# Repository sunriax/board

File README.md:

# BOARD Repository!

## Description

The BOARD repository is a set of Schematic and PCB files which can be used to build adapters for the STK500/STK600, Basys3 and other platforms. The design was made with Eagle and can be adapted easily. The Gerber files can also be found in the repository. We recommend to let [Elecrow](https://www.elecrow.com/) produce the PCB.

## Layouts

* [LCD Display Adapter](./display/display.md)
* [LCD Display Controller](./controller/controller.md)

## Important Notice

This files are valid for all repositories at the SUNriaX Github!
* [Readme](https://github.com/sunriax/manual/blob/master/README.md)
* [License](https://github.com/sunriax/manual/blob/master/LICENSE.md)
* [Warranty](https://github.com/sunriax/manual/blob/master/WARRANTY.md)

## Additional Information

You can find more additional information in the [manual](https://github.com/sunriax/manual/tree/master/docs) repository and/or visit the [WIKI](https://wiki.sunriax.at/) for further information (currently under construction).

If there are any further questions feel free to start an issue or contact us, we try to react as quick as possible.

---
**R. GÄCHTER, Rankweil Oct/2019**

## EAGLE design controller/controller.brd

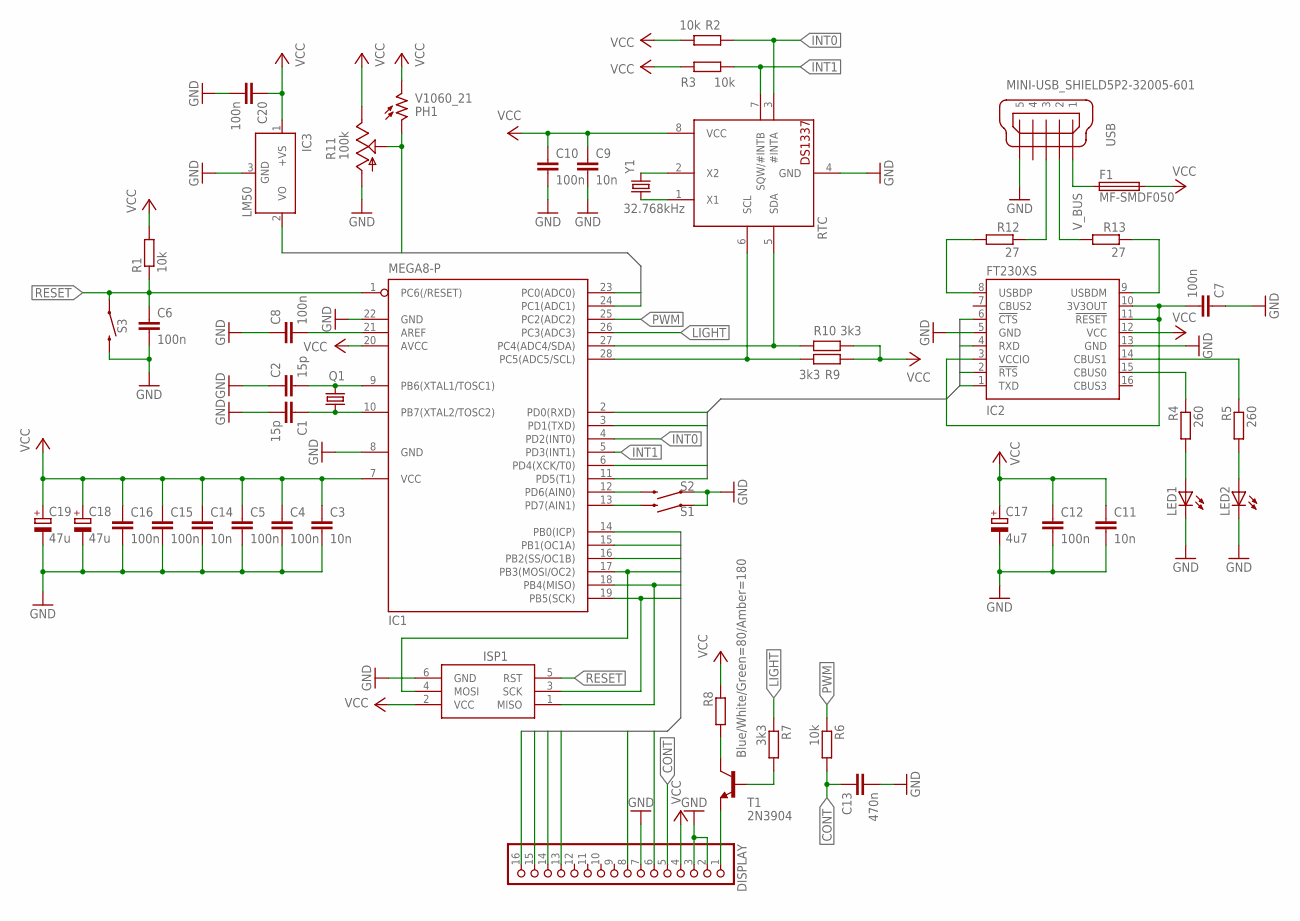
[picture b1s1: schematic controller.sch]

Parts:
C1, C2: 15p; C025-024X044
C3, C9, C11, C14: 10n; C025-024X044
C4, C5, C6, C7, C8, C10, C12, C15, C16, C20: 100n; C025-024X044
C13: 470n; C025-024X044
C17: 4u7; E1,8-4
C18, C19: 47u; E1,8-4
DISPLAY: PINHD-1X16; 1X16
F1: MF-SMDF050
IC1: MEGA8-P; DIL28-3
IC2: FT230XS; SSOP16
IC3: LM50; SOT23
ISP1: AVRISP-6; AVRISP
LED1, LED2: LED_ELD260; LED_LD260
PH1: V1060_21; TO-5_V10
Q1: CRYSTALHC18U-V; HC18U-V
R1, R2, R3, R6: 10k; 0207/10
R4, R5: 260; 0207/10
R7, R9, R10: 3k3; 0207/10
R8: Blue/White/Green=80/Amber=180; 0207/10
R11: 100k; CT6
R12, R13: 27; R0603
RTC: DS1337; DIL08-ROUND
S1, S2, S3: MOMENTARY-SWITCH-SPST-PTH-6.0MM; TACTILE_SWITCH_PTH_6.0MM
T1: 2N3904; TO92
USB: MINI-USB_SHIELD5P2-32005-601; 32005-601
Y1: 32.768kHz; CRYSTAL-PTH-2X6-CYL

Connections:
ADC0: IC1.23 (PC0(ADC0)), IC3.2 (VO)
ADC1: IC1.24 (PC1(ADC1)), PH1.1, R11.S
CONT: C13.1, DISPLAY.5, R6.2
CTS: IC1.6 (PD4(XCK/T0)), IC2.6 (!CTS)
DB4: DISPLAY.13, IC1.17 (PB3(MOSI/OC2)), ISP1.4 (MOSI)
DB5: DISPLAY.14, IC1.16 (PB2(SS/OC1B))
DB6: DISPLAY.15, IC1.15 (PB1(OC1A))
DB7: DISPLAY.16, IC1.14 (PB0(ICP))
E: DISPLAY.8, IC1.18 (PB4(MISO)), ISP1.1 (MISO)
GND: C1.2, C2.1, C3.2, C4.2, C5.2, C6.2, C7.1, C8.1, C9.2, C10.2, C11.2, C12.2, C13.2, C14.2, C15.2, C16.2, C17.-, C18.-, C19.-, C20.2, DISPLAY.2, DISPLAY.3, DISPLAY.7, IC1.8 (GND), IC1.22 (GND), IC2.5 (GND), IC2.13 (GND), IC3.3 (GND), ISP1.6 (GND), LED1.K (C), LED2.K (C), R11.A, RTC.4 (GND), S1.1, S2.1, S3.3 (2), USB.5
INT0: IC1.4 (PD2(INT0)), R2.1, RTC.3 (#INTA)
INT1: IC1.5 (PD3(INT1)), R3.2, RTC.7 (SQW/#INTB)
LIGHT: IC1.26 (PC3(ADC3)), R7.1
unnamed: C2.2, IC1.9 (PB6(XTAL1/TOSC1)), Q1.2
unnamed: C1.1, IC1.10 (PB7(XTAL2/TOSC2)), Q1.1
unnamed: R13.2, USB.2
unnamed: C8.2, IC1.21 (AREF)
unnamed: IC2.15 (CBUS0), R4.1
unnamed: R12.1, USB.3
unnamed: IC1.12 (PD6(AIN0)), S2.3 (2)
unnamed: IC1.13 (PD7(AIN1)), S1.3 (2)
unnamed: IC2.8 (USBDP), R12.2
unnamed: IC2.9 (USBDM), R13.1
unnamed: C7.2, IC2.3 (VCCIO), IC2.10 (3V3OUT), IC2.11 (!RESET)
unnamed: IC2.14 (CBUS1), R5.1
unnamed: LED1.A, R4.2
unnamed: LED2.A, R5.2
unnamed: DISPLAY.1, T1.3 (E)
unnamed: RTC.2 (X2), Y1.1
unnamed: R7.2, T1.2 (B)
unnamed: R8.2, T1.1 (C)
unnamed: IC1.28 (PC5(ADC5/SCL)), R9.2, RTC.6 (SCL)
unnamed: IC1.27 (PC4(ADC4/SDA)), R10.1, RTC.5 (SDA)
unnamed: RTC.1 (X1), Y1.2
PWM: IC1.25 (PC2(ADC2)), R6.1
RESET: C6.1, IC1.1 (PC6(/RESET)), ISP1.5 (RST), R1.1, S3.1
RS: DISPLAY.6, IC1.19 (PB5(SCK)), ISP1.3 (SCK)
RTS: IC1.11 (PD5(T1)), IC2.2 (!RTS)
RXD: IC1.3 (PD1(TXD)), IC2.4 (RXD)
TXD: IC1.2 (PD0(RXD)), IC2.1 (TXD)
VCC: C3.1, C4.1, C5.1, C9.1, C10.1, C11.1, C12.1, C14.1, C15.1, C16.1, C17.+, C18.+, C19.+, C20.1, DISPLAY.4, F1.2, IC1.7 (VCC), IC1.20 (AVCC), IC2.12 (VCC), IC3.1 (+VS), ISP1.2 (VCC), PH1.2, R1.2, R2.2, R3.1, R8.1, R9.1, R10.2, R11.E, RTC.8 (VCC)
V_BUS: F1.1, USB.1

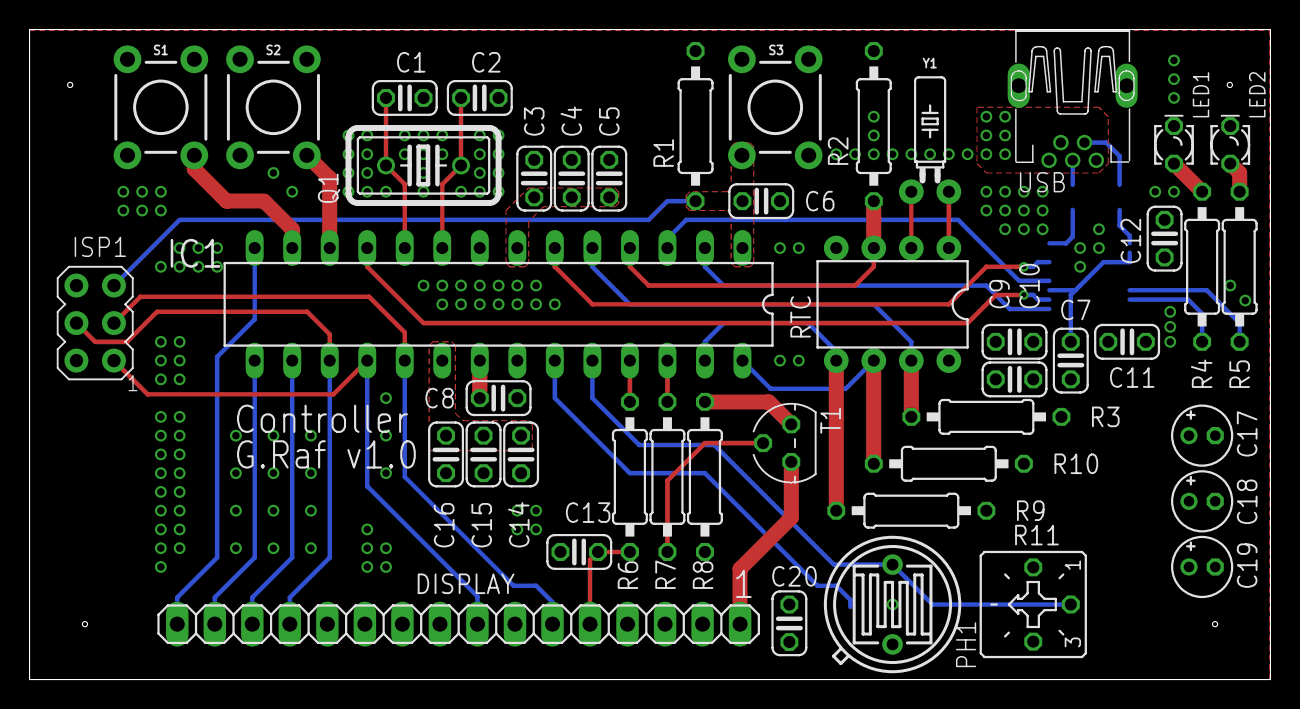
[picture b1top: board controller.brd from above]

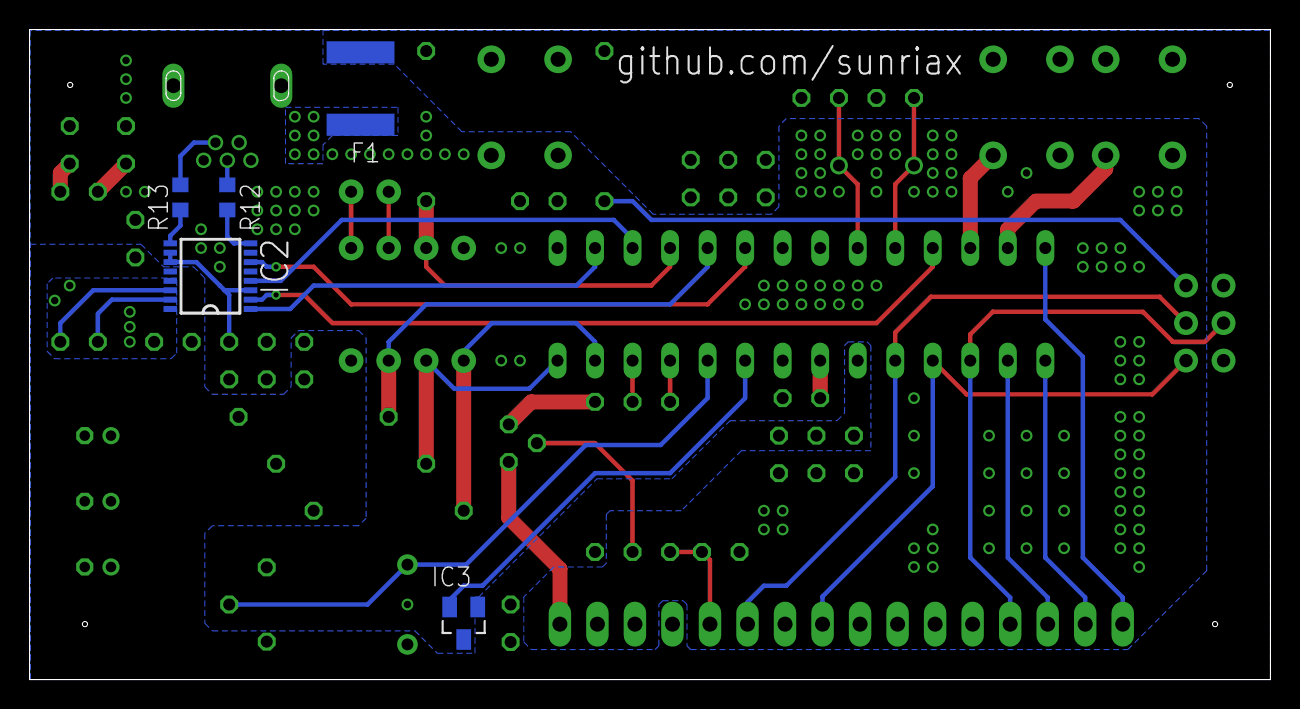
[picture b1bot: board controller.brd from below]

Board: 2 copper layers, 84.0 x 44.0 mm, 50 parts (5 on the bottom side), 42 nets.

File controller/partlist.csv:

Qty;Value;Device;Package;Parts;Description;MF;MPN;RS Online;
1;;CRYSTALHC18U-V;HC18U-V;Q1;CRYSTAL;;;814-9440;
2;;LED_ELD260;LED_LD260;LED1, LED2;LED;;;228-5938;228-5944
1;;PINHD-1X16;1X16;DISPLAY;PIN HEADER;;;674-1546;
1;100k;TRIM_US-CT6;CT6;R11;POTENTIOMETER;;;896-7138;
10;100n;C-EU025-024X044;C025-024X044;C4, C5, C6, C7, C8, C10, C12, C15, C16, C20;CAPACITOR, European symbol;;;538-1310;
4;10k;R-EU_0207/10;0207/10;R1, R2, R3, R7;RESISTOR, European symbol;;;707-8906;
4;10n;C-EU025-024X044;C025-024X044;C3, C9, C11, C14;CAPACITOR, European symbol;;;538-1180;
2;15p;C-EU025-024X044;C025-024X044;C1, C2;CAPACITOR, European symbol;;;133-5669;
2;260;R-EU_0207/10;0207/10;R4, R5;RESISTOR, European symbol;;;707-8845;
2;27;R-EU_R0603;R0603;R12, R13;RESISTOR, European symbol;;;866-7121;
1;2N3904;2N3904;TO92;T1;NPN TRANSISTOR;;;739-0442;
1;32.768kHz;CRYSTAL-32.768KHZPTH-2X6;CRYSTAL-PTH-2X6-CYL;Y1;32.768kHz Crystal;;;171-0553;
3;3k3;R-EU_0207/10;0207/10;R8, R9, R10;RESISTOR, European symbol;;;707-8883;
1;470n;C-EU025-024X044;C025-024X044;C13;CAPACITOR, European symbol;;;801-5394;
2;47u;CPOL-EUE1.8-4;E1,8-4;C18, C19;POLARIZED CAPACITOR, European symbol;;;228-6644;
1;4u7;CPOL-EUE1.8-4;E1,8-4;C17;POLARIZED CAPACITOR, European symbol;;;144-3950;
1;AVRISP-6;AVRISP-6;AVRISP;ISP1;AVR ISP HEADER;;;832-3705;832-3496
1;Blue/White/Green=80/Amber=180;R-EU_0207/10;0207/10;R6;RESISTOR, European symbol;;;707-8823;707-8833
1;DS1337;DS1337;DIL08-ROUND;RTC;DS1337 - Maxim RTC without battery backup;;;786-0749;
1;FT230XS;FT230XS;SSOP16;IC2;USB to BASIC UART IC;;;757-0010;
1;LM50;LM50;SOT23;IC3;SOT-23 Single-Supply Centigrade Temperature Sensor;;;535-9846;
1;MEGA8-P;MEGA8-P;DIL28-3;IC1;MICROCONTROLLER;;;131-0338;
1;MF-SMDF050;MF-SMDF050;MF-SMDF050;F1;MF-SMDF Series - PRC Resettable Fuses;;;647-7995;
1;MINI-USB_SHIELD5P2-32005-601;MINI-USB_SHIELD5P2-32005-601;32005-601;USB;MINI USB-B R/A DIP 5pol.;;;515-2005;
3;MOMENTARY-SWITCH-SPST-PTH-6.0MM;MOMENTARY-SWITCH-SPST-PTH-6.0MM;TACTILE_SWITCH_PTH_6.0MM;S1, S2, S3;Momentary Switch (Pushbutton) - SPST;;;479-1413;
1;V1060_21;V1060_21;TO-5_V10;PH1;Sensor Street Light control;;;914-6710;

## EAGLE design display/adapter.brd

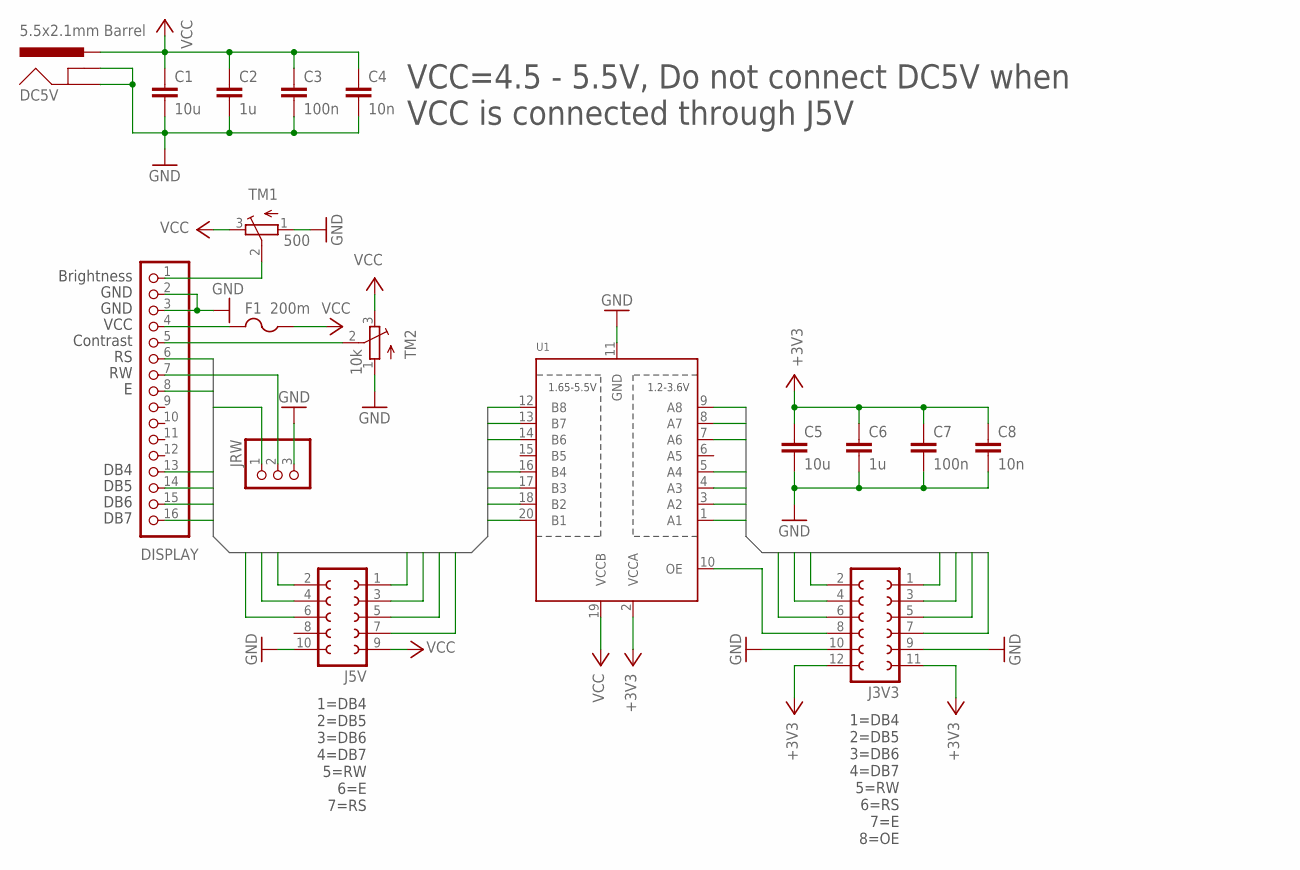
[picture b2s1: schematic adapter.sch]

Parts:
C1, C5: 10u; C0603
C2, C6: 1u; C0603
C3, C7: 100n; C0603
C4, C8: 10n; C0603
DC5V: 5.5x2.1mm Barrel; POWER_JACK_SMD
DISPLAY: PINHD-1X16; 1X16
F1: 200m; R1206
J3V3: FE06-2W
J5V: FE05-2W
JRW: PINHD-1X3/90; 1X03/90
TM1: 500; TC33X
TM2: 10k; TC33X
U1: TXB0108PWR; TSSOP20

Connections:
3DB4: J3V3.1, U1.1 (A1)
3DB5: J3V3.2, U1.3 (A2)
3DB6: J3V3.3, U1.4 (A3)
3DB7: J3V3.4, U1.5 (A4)
3E: J3V3.7, U1.9 (A8)
3RS: J3V3.6, U1.8 (A7)
3RW: J3V3.5, U1.7 (A6)
+3V3: C5.1, C6.1, C7.1, C8.1, J3V3.11, J3V3.12, U1.2 (VCCA)
DB4: DISPLAY.13, J5V.1, U1.20 (B1)
DB5: DISPLAY.14, J5V.2, U1.18 (B2)
DB6: DISPLAY.15, J5V.3, U1.17 (B3)
DB7: DISPLAY.16, J5V.4, U1.16 (B4)
E: DISPLAY.8, J5V.6, U1.12 (B8)
GND: C1.2, C2.2, C3.2, C4.2, C5.2, C6.2, C7.2, C8.2, DC5V.GND (GNDBREAK), DC5V.P$4 (GND), DISPLAY.2, DISPLAY.3, J3V3.9, J3V3.10, J5V.10, JRW.3, TM1.1 (A), TM2.1 (A), U1.11 (GND)
unnamed: DISPLAY.5, TM2.2 (S)
unnamed: DISPLAY.1, TM1.2 (S)
unnamed: DISPLAY.4, F1.2
unnamed: DISPLAY.7, JRW.2
unnamed: J3V3.8, U1.10 (OE)
RS: DISPLAY.6, J5V.7, U1.13 (B7)
RW: J5V.5, JRW.1, U1.14 (B6)
VCC: C1.1, C2.1, C3.1, C4.1, DC5V.VIN0 (PWR), F1.1, J5V.9, TM1.3 (E), TM2.3 (E), U1.19 (VCCB)

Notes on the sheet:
VCC=4.5 - 5.5V, Do not connect DC5V when VCC is connected through J5V
Brightness
GND
VCC
Contrast
DB4
DB5
DB6
DB7
1=DB4 2=DB5 3=DB6 4=DB7 5=RW 6=E 7=RS
1=DB4 2=DB5 3=DB6 4=DB7 5=RW 6=RS 7=E 8=OE

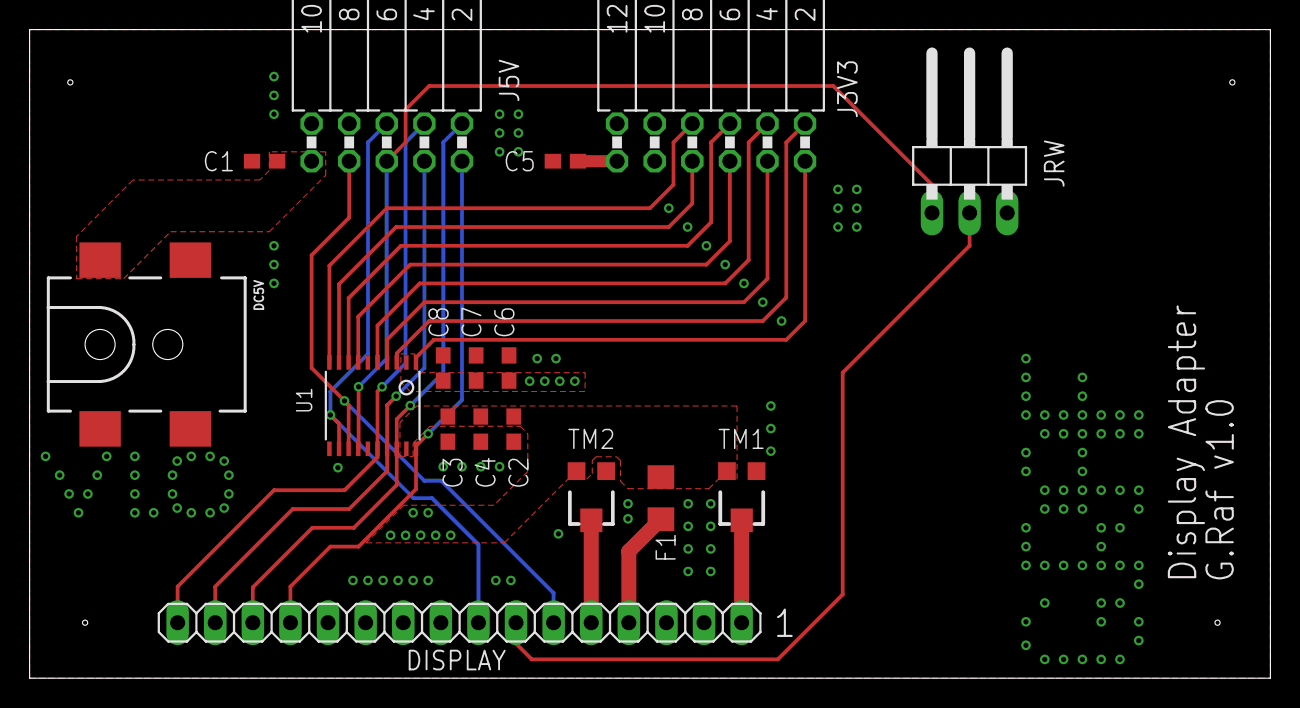
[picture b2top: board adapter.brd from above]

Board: 2 copper layers, 83.8 x 43.8 mm, 17 parts (0 on the bottom side), 22 nets.

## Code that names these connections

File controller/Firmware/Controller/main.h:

/* -------------------------------------
 * SUNriaX Project
 * www.sunriax.at
 * -------------------------------------
 * Hardware: Controller
 * Platform: ATmega8
 * -------------------------------------
 * Name: CONTROLLER
 * Ver.: 1.0 Release
 * Type: Executeable
 * Text: Example Software for the
 *       Controller. Display Time and
 *       Date from DS1337, temperature
 *       and light intensity. Backlight
 *       of the display is controlled
 *       by the light sensor. Data can
 *       also be catched over uart
 * -------------------------------------
 */

#ifndef MAIN_H_
#define MAIN_H_

// System
#define F_CPU 16000000UL

// EEPROM Data
#define EEI 0

// Display
#define DISPLAY_CTRL_DDR DDRC
#define DISPLAY_CTRL_PORT PORTC
#define CONTRAST   PC2
#define BACKLIGHT  PC3

// Sensor
#define SENSOR_DDR  DDRC
#define SENSOR_PORT PORTC
#define TEMPRATURE PC0
#define INTENSITY  PC1

// DS1337 Interrupts
#define DS1337_DDR  DDRD
#define DS1337_PORT PORTD
#define INTA PD2
#define INTB PD3

// Push-Button
#define SWITCH_DDR  DDRD
#define SWITCH_PORT PORTD
#define SWITCH_PIN  PIND
#define S0 PD6
#define S1 PD7

// Libraries
#include <stdlib.h>
#include <avr/io.h>
#include <avr/interrupt.h>
#include <avr/eeprom.h>
#include <util/delay.h>

#include "../Library/adc.h"
#include "../Library/lcd.h"
#include "../Library/twi.h"
#include "../Library/uart.h"
#include "../Library/eeprom.h"
#include "../Library/ds1337.h"

#endif /* MAIN_H_ */

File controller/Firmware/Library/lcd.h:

/* -------------------------------------
 * SUNriaX Project
 * www.sunriax.at
 * -------------------------------------
 * Hardware: STKX00
 * Platform: ATmeag8/16/2560
 * -------------------------------------
 * Name: adc
 * Ver.: 1.0 Release
 * Type: Library
 * Text: Routines for initializing and
 *       display characters onto the
 *       LCD @ 4 bit mode
 * -------------------------------------
 */

#ifndef LCD_H_
#define LCD_H_

// Definition of SYSTEM parameters

#ifndef F_CPU			// Systemclock
	#define F_CPU 16000000UL
#endif

// Definition of LCD parameters

#ifndef F_LCD			// LCD enable clock
	#define F_LCD 100000UL
#endif

// LCD control directives
#ifndef LCD_DDR_CTRL	// LCD control direction register
	#define LCD_DDR_CTRL DDRB
#endif

#ifndef LCD_PORT_CTRL	// LCD control port register
	#define LCD_PORT_CTRL PORTB
#endif

#ifndef LCD_RS			// LCD register select
	#define LCD_RS PB5
#endif

#ifndef LCD_E			// LCD start data read/write
	#define LCD_E PB4
#endif

// LCD data directives
#ifndef LCD_DDR_DATA	// LCD data direction register
	#define LCD_DDR_DATA DDRB
#endif

#ifndef LCD_PORT_DATA	// LCD control direction register
	#define LCD_PORT_DATA PORTB
#endif

#ifndef LCD_DB0			// LCD data bit 0 (LCD display bit 4)
	#define LCD_DB0 PB3
#endif

#ifndef LCD_DB1			// LCD data bit 1 (LCD display bit 5)
	#define LCD_DB1 PB2
#endif

#ifndef LCD_DB2			// LCD data bit 2 (LCD display bit 6)
	#define LCD_DB2 PB1
#endif

#ifndef LCD_DB3		// LCD data bit 3 (LCD display bit 7)
	#define LCD_DB3 PB0
#endif

// LCD display parameters
#ifndef LCD_COLUMNS		// LCD display columns/row (1 - 20)
	#define LCD_COLUMNS 16
#endif

#ifndef LCD_START_ADDR	// Start position of the LCD RAM
	#define LCD_START_ADDR 0x80
#endif

// LCD time/instruction codes (!!! Do not change !!!)

// LCD time directives
#ifndef LCD_STARTUP_TIME	// LCD startup time in ms
	#define LCD_STARTUP_TIME 15
#endif

#ifndef LCD_CLEAR_TIME	// LCD startup time in ms
	#define LCD_CLEAR_TIME 2
#endif

#ifndef LCD_RETURN_TIME	// LCD return home time in ms
	#define LCD_RETURN_TIME 2
#endif

#ifndef LCD_ENTRY_TIME	// LCD entry mode time in us
	#define LCD_ENTRY_TIME 42
#endif

// #ifndef LCD_DISPLAY_TIME	// LCD display time in us
//	#define LCD_DISPLAY_TIME 42
// #endif

// #ifndef LCD_SHIFT_TIME	// LCD shift time in us
// 	#define LCD_SHIFT_TIME 42
// #endif

#ifndef LCD_FUNCTION_TIME	// LCD function time in us
	#define LCD_FUNCTION_TIME 42
#endif

#ifndef LCD_WRITE_TIME		// LCD WRITE time in us
	#define LCD_WRITE_TIME 42
#endif

#ifndef LCD_CMD_TIME		// LCD COMMAND time in us
	#define LCD_CMD_TIME 42
#endif

// LCD instruction directives
#ifndef LCD_CLEAR			// LCD clear display instruction
	#define LCD_CLEAR           0b00000001
#endif

#ifndef LCD_HOME			// LCD return home instruction
	#define LCD_HOME            0b00000010
#endif

#ifndef LCD_ENTRY			// LCD entry mode set instruction
	#define LCD_ENTRY           0b00000100
	#define LCD_ENTRY_INCREMENT 0b00000010
	#define LCD_ENTRY_SHIFT     0b00000001
#endif

#ifndef LCD_DISPLAY			// LCD display set instruction
	#define LCD_DISPLAY         0b00001000
	#define LCD_DISPLAY_ON      0b00000100
	#define LCD_CURSOR_ON       0b00000010
	#define LCD_BLINK_ON        0b00000001
#endif

#ifndef LCD_SHIFT			// LCD shift instruction
	#define LCD_SHIFT           0b00010000
	#define LCD_SHIFT_DISPLAY   0b00001000
	#define LCD_SHIFT_RIGHT     0b00000100
#endif

#ifndef LCD_FUNCTION		// LCD function instruction
	#define LCD_FUNCTION        0b00100000
	#define LCD_FUNCTION_8BIT   0b00010000
	#define LCD_FUNCTION_2LINE  0b00001000
	#define LCD_FUNCTION_5x10	0b00000100
#endif

#ifndef LCD_CGADDR			// LCD CGADDR instruction
	#define LCD_CGADDR          0b01000000
	#define LCD_CGADDR_CHAR0    0b00000000
	#define LCD_CGADDR_CHAR1    0b00000001
	#define LCD_CGADDR_CHAR2    0b00000010
	#define LCD_CGADDR_CHAR3    0b00000011
	#define LCD_CGADDR_CHAR4    0b00000100
	#define LCD_CGADDR_CHAR5    0b00000101
	#define LCD_CGADDR_CHAR6    0b00000110
	#define LCD_CGADDR_CHAR7    0b00000111
	#define LCD_CGADDDR_MAX     7
#endif

#ifndef LCD_DDADDR			// LCD DDADDR instruction
	#define LCD_DDADDR          0b10000000
#endif

#ifndef LCD_SPACE			// Space character
	#define LCD_SPACE 0x20
#endif

#ifndef LCD_NULL			// End character
	#define LCD_NULL 0x00
#endif

#include <stdlib.h>
#include <avr/io.h>
#include <util/delay.h>

void lcd_init(void);
void lcd_disable(void);
void lcd_clock(void);
void lcd_set(unsigned char data);
void lcd_cmd(unsigned char instruction);
void lcd_char(char data);
void lcd_string(const char *data);
void lcd_clear(void);
void lcd_home(void);
void lcd_cursor(unsigned char x, unsigned char y);
void lcd_pattern(unsigned char address, const unsigned char *data);
void lcd_ul2ascii(unsigned long data, unsigned char base, unsigned char length);
void lcd_sl2ascii(const signed long data, unsigned char base, unsigned char length);
void lcd_d2ascii(const double data, unsigned char length, unsigned char precision);

#endif /* LCD_H_ */

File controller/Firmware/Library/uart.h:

/* -------------------------------------
 * SUNriaX Project
 * www.sunriax.at
 * -------------------------------------
 * Hardware: STKX00
 * Platform: ATmeag8/16/2560
 * -------------------------------------
 * Name: adc
 * Ver.: 1.0 Release
 * Type: Library
 * Text: Routines for initializing and
 *       communication over UART
 * -------------------------------------
 */

#ifndef UART_H_
#define UART_H_

// Definition of SYSTEM parameters

#ifndef F_CPU	// Systemclock
	#define F_CPU 16000000UL
#endif

// Definition of UART parameters

#ifndef BAUD	// UART baudrate
	#define BAUD 9600UL
#endif

#ifndef DATASIZE	//UART datasize
	#define DATASIZE 0x08	// 5 Bit = 0x05
							// 6 Bit = 0x06
							// 7 Bit = 0x07
							// 8 Bit = 0x08
#endif

#ifndef PARITY
	#define PARITY 0x00		// 0x00 = None
							// 0x01 = Reserved
							// 0x02 = Even Parity
							// 0x03 = Odd Parity
#endif

#ifndef STOPBITS
	#define STOPBITS 0x01	// 0x01 = 1 Stopbit
							// 0x02 = 2 Stopbit
#endif

#ifndef U2XEN	// Sample rate (defined = 8 Samples/Bit | undefined = 16 Samples/Bit)
	#define U2XEN
#endif

// Definition of UART processing (Enabled = Interrupt/Disabled = Polling)

// !!!!!!!!!!!!!!!!!!!!!!!!!!!!!!!!!!!!!!!!!!!!!!!
// ! Interrupts are not included in this library !
// ! If interrupts are used, disable the polling !
// ! by uncommenting the next lines              !
// !!!!!!!!!!!!!!!!!!!!!!!!!!!!!!!!!!!!!!!!!!!!!!!

//#ifndef UARTRXCIE	// Receiver Interrupt based processing
//	#define UARTRXCIE
//#endif

//#ifndef UARTTXCIE	// Transmitter Interrupt based processing
//	#define UARTTXCIE
//#endif

//#ifndef UARTUDRIE	// Transmitter Interrupt based processing
//	#ifndef UARTTXCIE
//		#define UARTUDRIE
//	#else
//		#undef UARTUDRIE
//	#endif
//#endif

// UART
#ifndef UART_DDR
	#define UART_DDR  DDRD
#endif

#ifndef UART_PORT
	#define UART_PORT PORTD
#endif

#ifndef UART_PIN
	#define UART_PIN PIND
#endif

#ifndef CTS
	#define CTS PD4
	
	#ifndef CTS_PULLUP
		#define CTS_PULLUP
	#endif
#endif

#ifndef RTS
	#define RTS PD5
#endif

#include <stdlib.h>
#include <avr/io.h>
#include <avr/interrupt.h>

void uart_init(void);
void uart_disable(void);
void uart_reset(void);

#ifdef RTS
	void uart_rts(unsigned char status);
#endif

#ifdef CTS
	unsigned char uart_cts(void);
#endif

#ifndef UARTTXCIE
	#ifndef UARTUDRIE
		void uart_setchar(unsigned char data);
		void uart_setstring(char *string);
		void uart_setvalue(unsigned char data, unsigned char radix);
		
		void uart_linebreak(void);
		void uart_2linebreak(void);
		void uart_delimiter(unsigned char delimiter);
		
	#endif
#endif

#ifndef UARTRXCIE
	unsigned char uart_getchar(unsigned char *data, unsigned char echo);
	unsigned char uart_getstring(unsigned char *string, unsigned char length, unsigned char delimiter, unsigned char echo);
#endif

#endif /* UART_H_ */

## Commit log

2018-10-27 Update
    Changed some things in README.md
2018-10-27 Update
    Added display adapter JPW setting
2018-10-27 Update
    Added partlist and gerber files. Updated some things on board
2018-10-31 Update
    Error correction of Display header position.
2018-10-31 Update
    Corrected some things in display.md
2018-10-31 Update
    Because i can´t read, the display header had to be repositioned a second time...
2018-10-31 Update
    Board should now be completed
2018-11-01 Update
    Added a new design (controller) and corrected again some things in the display project...
2018-11-02 Update
    Completed the controller design
2018-11-02 Update
    Corrected some things and added partlist to the controller project
2018-11-03 Update
    Corrected wrong direction of the display header
2018-11-03 Update
    Schematic update
2019-04-25 Update
    Added silkscreen PDF and seperated SMD partlist
2019-05-03 Update
    Added startup files for Firmware development
2019-11-01 Corrected partlist
2019-11-01 Changed partlist
    Added , instead of ;
2019-11-01 Correction
    Changed background color of the boards and optimized pdf´s
2019-11-01 Added BOM
2019-11-03 Firmware init
    Started developing the bootloader
2019-11-07 Initial
    Initial bootloader and (demo) controller software
2019-11-07 CI and description adapted
    Changed some things for travis-ci and adaptet the description and changed the partlist.
2019-11-07 Corrected CI
    Corrected failed change directory (cd) command

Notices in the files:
README.md:
License: GPL v3
parts and their libraries:
SparkFun-Switches: Licensing: Creative Commons ShareAlike 4.0 International - https://creativecommons.org/licenses/by-sa/4.0
